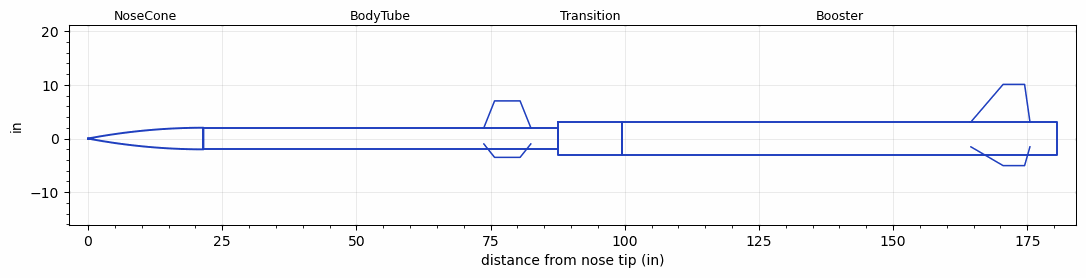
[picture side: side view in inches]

<RASAeroDocument>
 <FileVersion>2</FileVersion>
 <RocketDesign>
  <NoseCone>
   <Length>21.5</Length>
   <Diameter>4.026</Diameter>
   <Shape>Tangent Ogive</Shape>
   <Location>0</Location>
  </NoseCone>
  <BodyTube>
   <Length>66</Length>
   <Diameter>4.026</Diameter>
   <Location>21.5</Location>
   <Fin>
    <Count>3</Count>
    <Chord>8.75</Chord>
    <Span>5</Span>
    <SweepDistance>2</SweepDistance>
    <TipChord>4.75</TipChord>
    <Thickness>0.125</Thickness>
    <Location>13.75</Location>
    <AirfoilSection>Square</AirfoilSection>
   </Fin>
  </BodyTube>
  <Transition>
   <Length>12</Length>
   <Diameter>6.18</Diameter>
   <Location>87.5</Location>
   <RearDiameter>6.18</RearDiameter>
  </Transition>
  <Booster>
   <Length>81</Length>
   <Diameter>6.18</Diameter>
   <InsideDiameter>6.18</InsideDiameter>
   <Location>99.5</Location>
   <ShoulderLength>0</ShoulderLength>
   <Fin>
    <Count>3</Count>
    <Chord>11</Chord>
    <Span>7</Span>
    <SweepDistance>6</SweepDistance>
    <TipChord>4</TipChord>
    <Thickness>0.125</Thickness>
    <Location>16</Location>
    <AirfoilSection>Square</AirfoilSection>
   </Fin>
  </Booster>
  <Surface>Smooth (Zero Roughness)</Surface>
  <ModifiedBarrowman>False</ModifiedBarrowman>
  <Turbulence>False</Turbulence>
  <UseBooster1>False</UseBooster1>
  <UseBooster2>False</UseBooster2>
 </RocketDesign>
 <LaunchSite>
  <Altitude>0</Altitude>
  <Pressure>0</Pressure>
  <RodAngle>0</RodAngle>
  <RodLength>4</RodLength>
  <Temperature>74</Temperature>
  <WindSpeed>0</WindSpeed>
 </LaunchSite>
 <Recovery>
  <Altitude1>1000</Altitude1>
  <Altitude2>1000</Altitude2>
  <DeviceType1>None</DeviceType1>
  <DeviceType2>None</DeviceType2>
  <Event1>False</Event1>
  <Event2>False</Event2>
  <Size1>1</Size1>
  <Size2>1</Size2>
  <EventType1>None</EventType1>
  <EventType2>None</EventType2>
  <CD1>1.33</CD1>
  <CD2>1.33</CD2>
 </Recovery>
</RASAeroDocument>
